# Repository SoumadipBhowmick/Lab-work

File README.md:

# Lab-Work

Experiments performed in my undergraduate curriculum at IISER Mohali. 

## Required packages:
-----------------------------
* MatPlotLib
* SciPy
* NumPy
* pandas
* [SciencePlots](https://github.com/garrettj403/SciencePlots)

# Learn:
-----------------
Repository has the Essentials folder for referencing the libraries used with a variety of useful functions.
(More notes work in progress)

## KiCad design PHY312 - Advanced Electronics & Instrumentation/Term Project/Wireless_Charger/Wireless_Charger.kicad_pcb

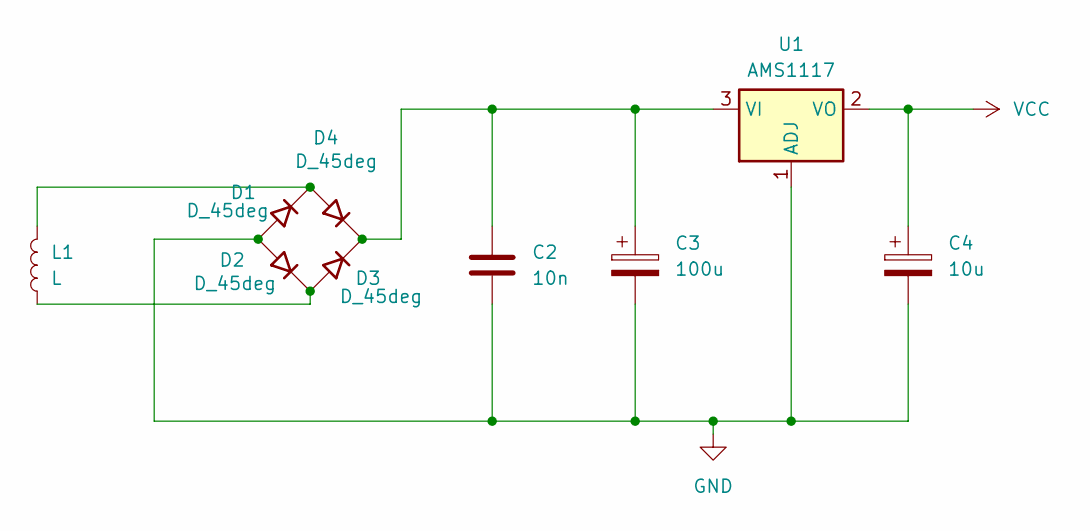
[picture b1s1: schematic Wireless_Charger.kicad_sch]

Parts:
C2: 10n; C_Disc_D5.0mm_W2.5mm_P2.50mm
C3: 100u; CP_Radial_D8.0mm_P5.00mm
C4: 10u; CP_Radial_D10.0mm_P5.00mm
D1, D2, D3, D4: D_45deg; D_DO-41_SOD81_P10.16mm_Horizontal
L1: L; L_Axial_L20.3mm_D12.1mm_P28.50mm_Horizontal_Vishay_IHA-101
U1: AMS1117; TO-220-3_Vertical

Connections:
GND: C2.2, C3.2, C4.2, D1.2 (A), D2.2 (A), U1.1 (ADJ)
unnamed: D1.1 (K), D4.2 (A), L1.2
unnamed: D2.1 (K), D3.2 (A), L1.1
unnamed: C2.1, C3.1, D3.1 (K), D4.1 (K), U1.3 (VI)
VCC: C4.1, U1.2 (VO)

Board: 2 copper layers, 9 parts (0 on the bottom side), 5 nets, no tracks yet.

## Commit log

2023-03-21 created helmhortz.ipynb
2023-03-28 coil graph done
2023-03-28 created curve fit & matplot notes
2023-03-28 fully optimized
2023-03-30 Finished it finally
2023-03-30 Owari da
2023-03-30 Graphs done
2023-04-05 Initial calculations
2023-04-06 Mostly done
2023-04-12 Did all the graphs
2023-04-20 Theoretical calculations almost done
2023-04-26 Redid all the graphs, added frequency dist.
2023-04-27 Completed Biot-Savart
2023-05-04 Started Stephen's const.
2023-08-17 Organized directories
2023-09-06 august dump
2024-04-22 Sem 4 finisimo
2025-05-16 added sem 5
2025-05-16 added sem 6
